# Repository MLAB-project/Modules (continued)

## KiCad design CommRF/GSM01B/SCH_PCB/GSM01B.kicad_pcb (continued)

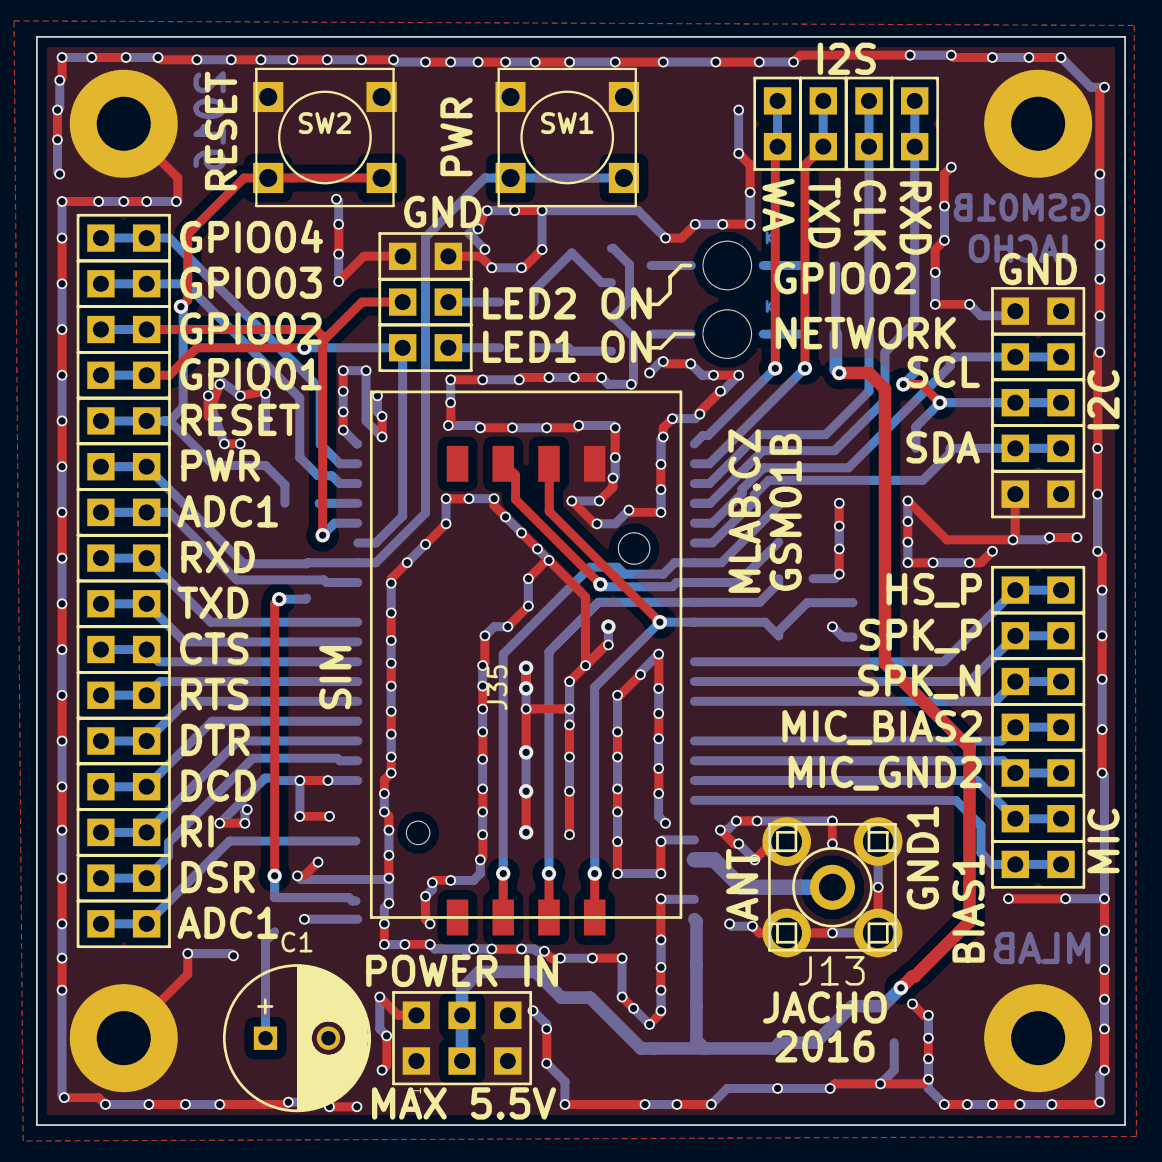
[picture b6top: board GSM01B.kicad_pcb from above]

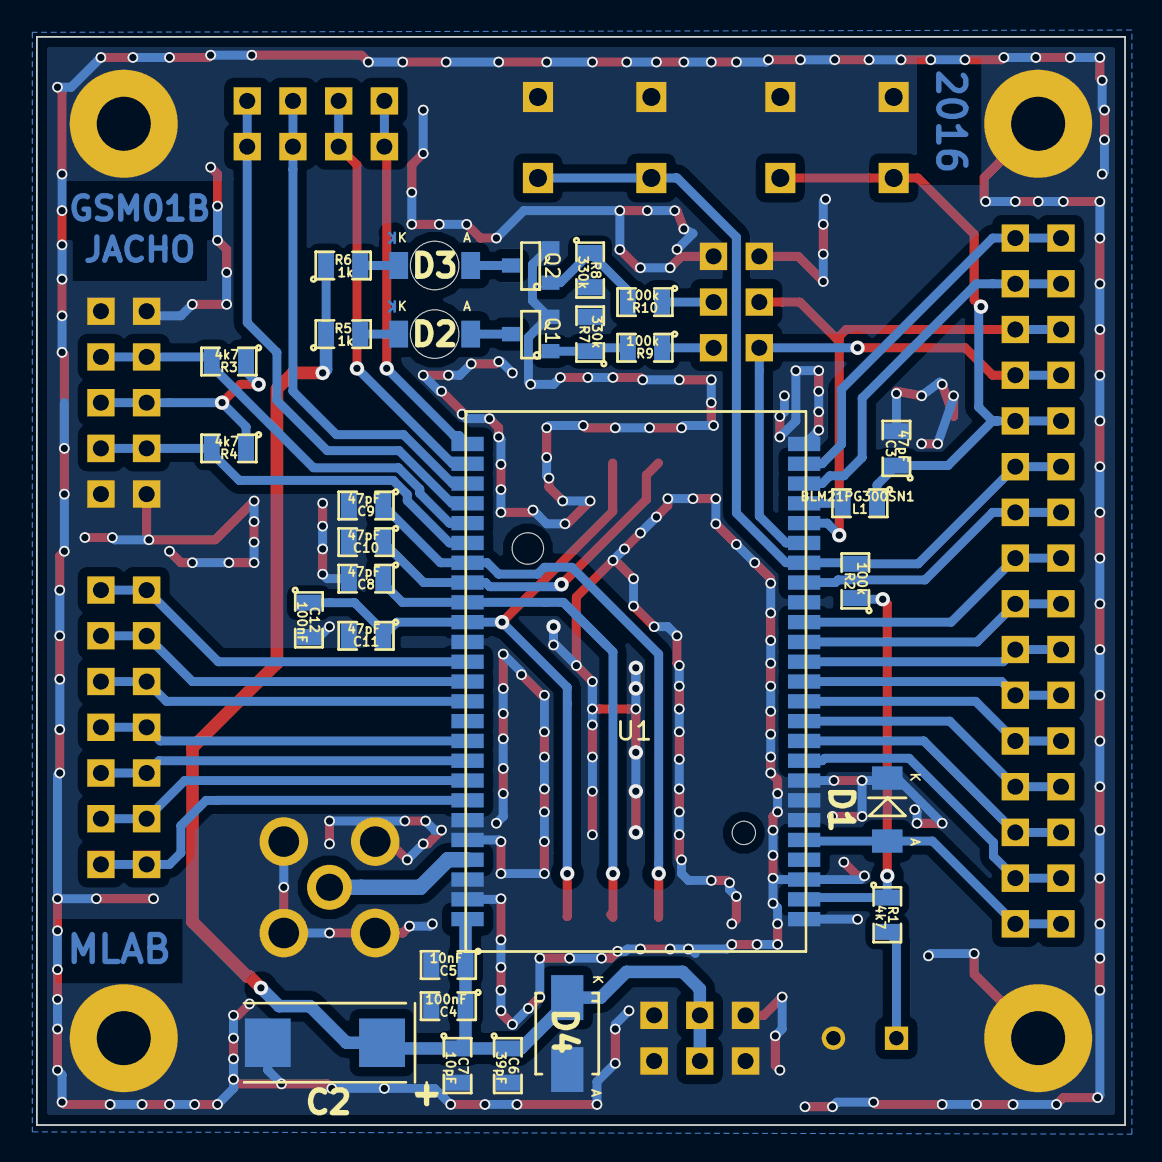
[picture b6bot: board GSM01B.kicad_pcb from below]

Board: 2 copper layers, 60.5 x 60.5 mm, 74 parts (29 on the bottom side), 48 nets.

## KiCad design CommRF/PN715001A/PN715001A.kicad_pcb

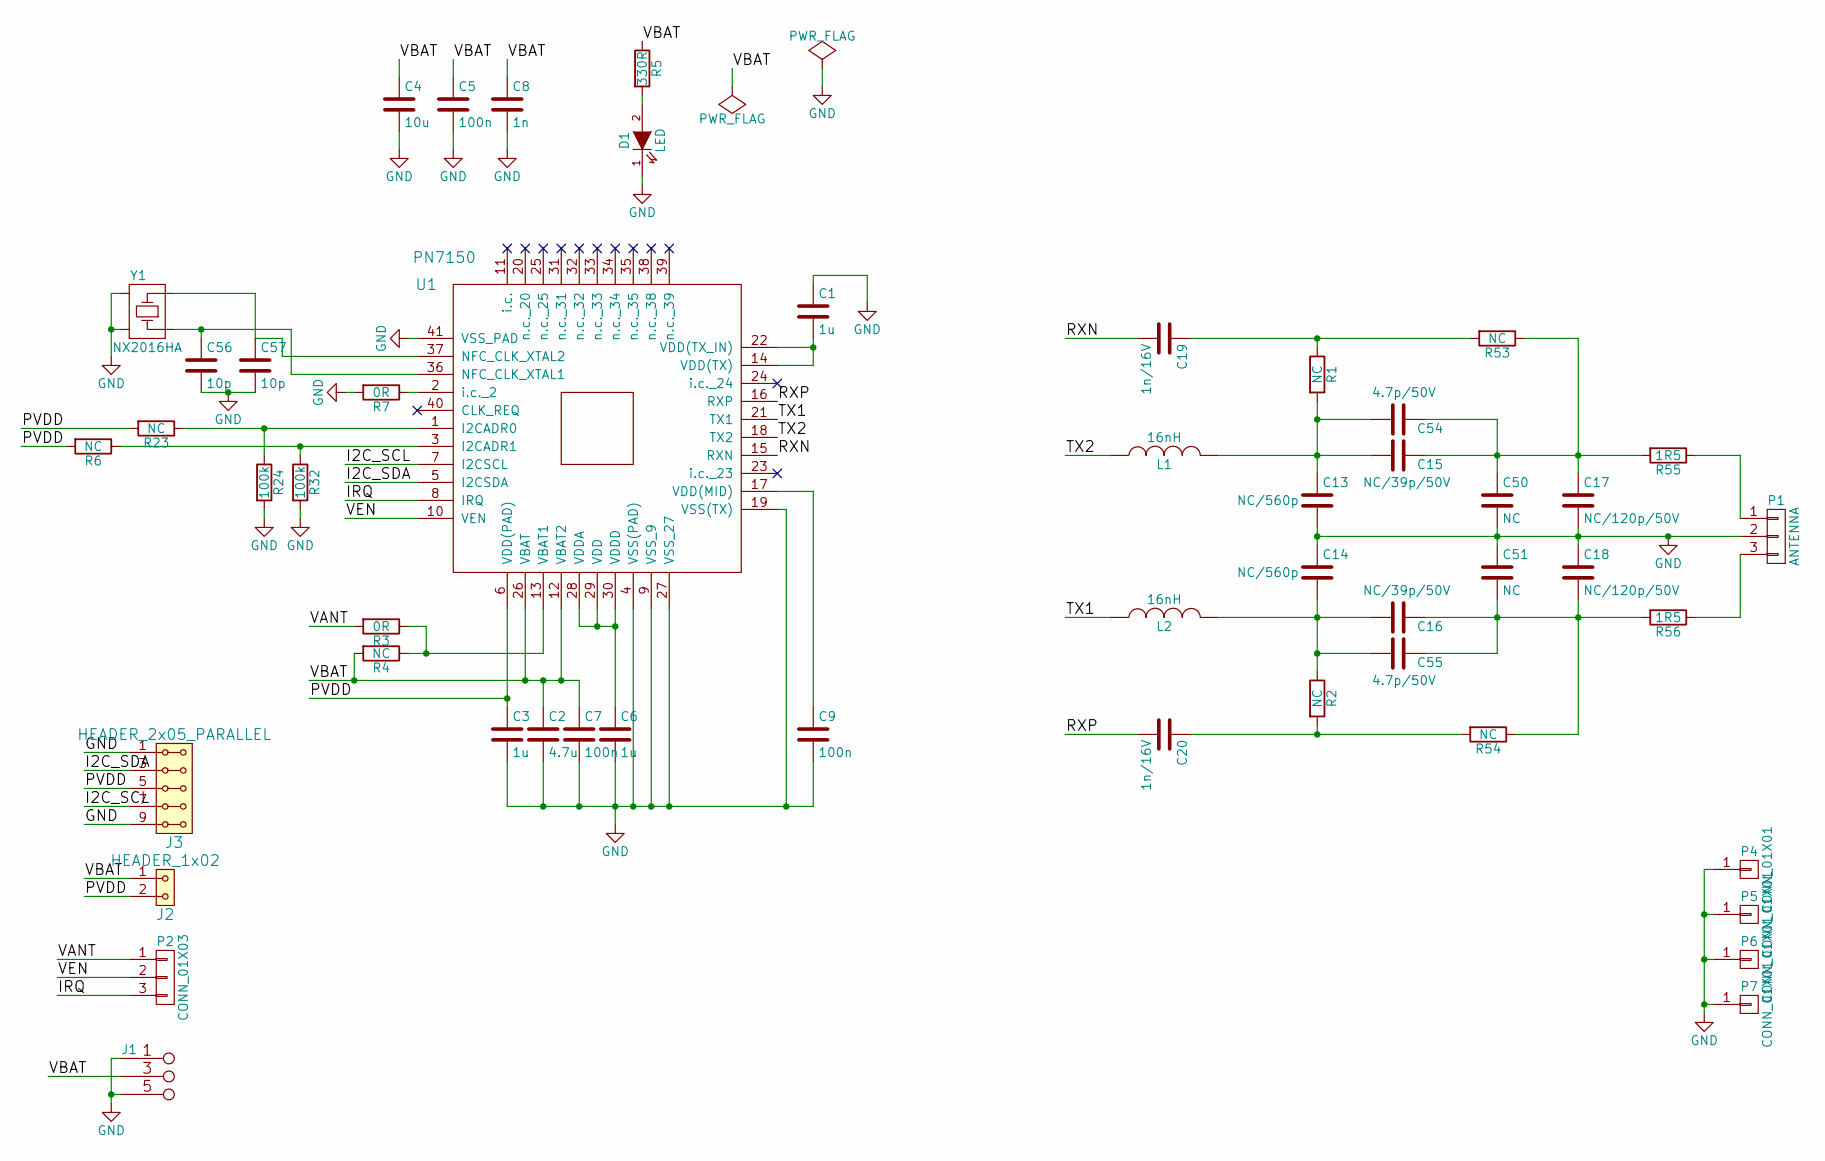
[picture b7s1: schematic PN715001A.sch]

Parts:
C1, C3, C6: 1u; C_0603
C2: 4.7u; C_0603
C4: 10u; C_0805
C5, C7, C9: 100n; C_0603
C8: 1n; C_0603
C13, C14: NC/560p; C_0603
C15, C16: NC/39p/50V; C_0603
C17, C18: NC/120p/50V; C_0603
C19, C20: 1n/16V; C_0603
C50, C51: NC; C_0603
C54, C55: 4.7p/50V; C_0603
C56, C57: 10p; C_0603
D1: LED; LED_1206
J1: PWR +3.3V; Straight_2x03
J2: HEADER_1x02; Straight_1x02
J3: HEADER_2x05_PARALLEL; Straight_2x05
L1, L2: 16nH; R_0603
P1: ANTENNA; Straight_1x03
P2: CONN_01X03; Straight_1x03
P4, P5, P6, P7: CONN_01X01; MountingHole_3mm
R1, R2, R4, R6, R23, R53, R54: NC; R_0603
R3, R7: 0R; R_0603
R5: 330R; R_0603
R24, R32: 100k; R_0603
R55, R56: 1R5; R_0603
U1: PN7150; QFN-40-1EP_6x6mm_Pitch0.5mm
Y1: NX2016HA

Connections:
/I2C_SCL: J3.7, J3.8, U1.7 (I2CSCL)
/I2C_SDA: J3.3, J3.4, U1.5 (I2CSDA)
/IRQ: P2.3, U1.8 (IRQ); also elsewhere on the board
/PVDD: C3.1, J2.2, J3.5, J3.6, R6.2, R23.2, U1.6 (VDD(PAD))
/RXN: C19.2, U1.15 (RXN)
/RXP: C20.2, U1.16 (RXP)
/TX1: L2.1, U1.21 (TX1)
/TX2: L1.1, U1.18 (TX2)
/VANT: C1.2, U1.14 (VDD(TX)), U1.22 (VDD(TX_IN)); also elsewhere on the board
/VBAT: C2.1, C4.1, C5.1, C7.1, C8.1, J1.3 (4), J1.4, J2.1, R4.2, R5.1, U1.12 (VBAT2), U1.26 (VBAT)
/VEN: P2.2, U1.10 (VEN); also elsewhere on the board
GND: C1.1, C2.2, C3.2, C4.2, C5.2, C6.2, C7.2, C8.2, C9.2, C13.2, C14.1, C17.2, C18.1, C50.2, C51.1, C56.2, C57.2, D1.1 (K), J1.1 (2), J1.2, J1.5 (6), J1.6, J3.1, J3.2, J3.9, J3.10, P1.2, P4.1, P5.1, P6.1, P7.1, R7.2, R24.2, R32.2, U1.4 (VSS(PAD)), U1.9 (VSS_9), U1.19 (VSS(TX)), U1.27 (VSS_27), U1.41 (VSS_PAD), Y1.2, Y1.4
unnamed: C6.1, U1.28 (VDDA), U1.29 (VDD), U1.30 (VDDD)
unnamed: C9.1, U1.17 (VDD(MID))
unnamed: C13.1, C15.2, C54.2, L1.2, R1.2
unnamed: C14.2, C16.2, C55.2, L2.2, R2.1
unnamed: C15.1, C17.1, C50.1, C54.1, R53.1, R55.2
unnamed: C16.1, C18.2, C51.2, C55.1, R54.1, R56.2
unnamed: C19.1, R1.1, R53.2
unnamed: C20.1, R2.2, R54.2
unnamed: C56.1, U1.36 (NFC_CLK_XTAL1), Y1.1
unnamed: C57.1, U1.37 (NFC_CLK_XTAL2), Y1.3
unnamed: D1.2 (A), R5.2
unnamed: P1.1, R55.1
unnamed: P1.3, R56.1
unnamed: P2.1, R3.2
unnamed: R3.1, R4.1, U1.13 (VBAT1)
unnamed: R7.1, U1.2 (i.c._2)
unnamed: R23.1, R24.1, U1.1 (I2CADR0)
unnamed: R6.1, R32.1, U1.3 (I2CADR1)

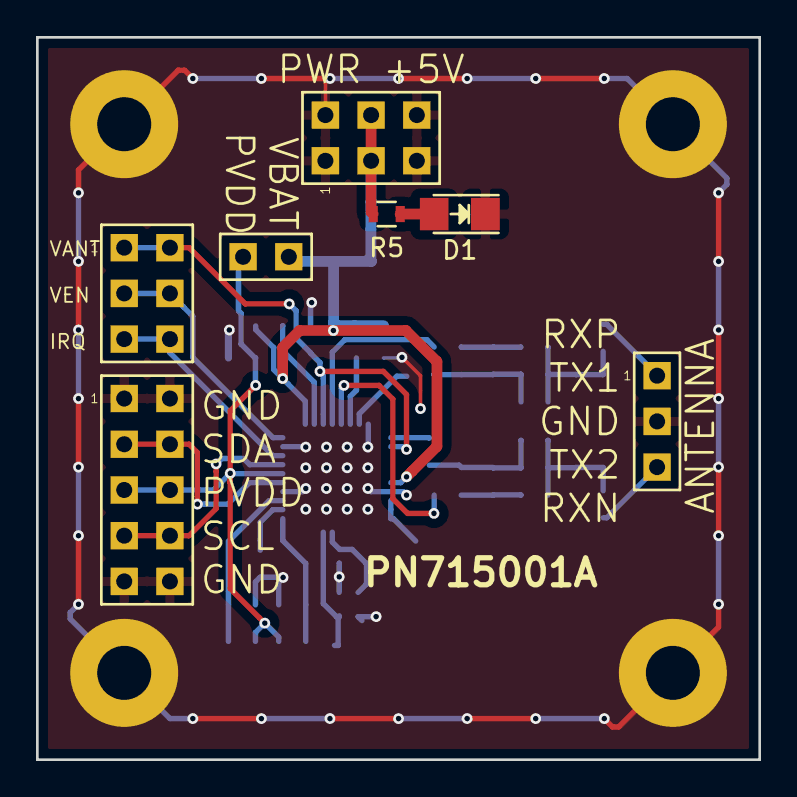
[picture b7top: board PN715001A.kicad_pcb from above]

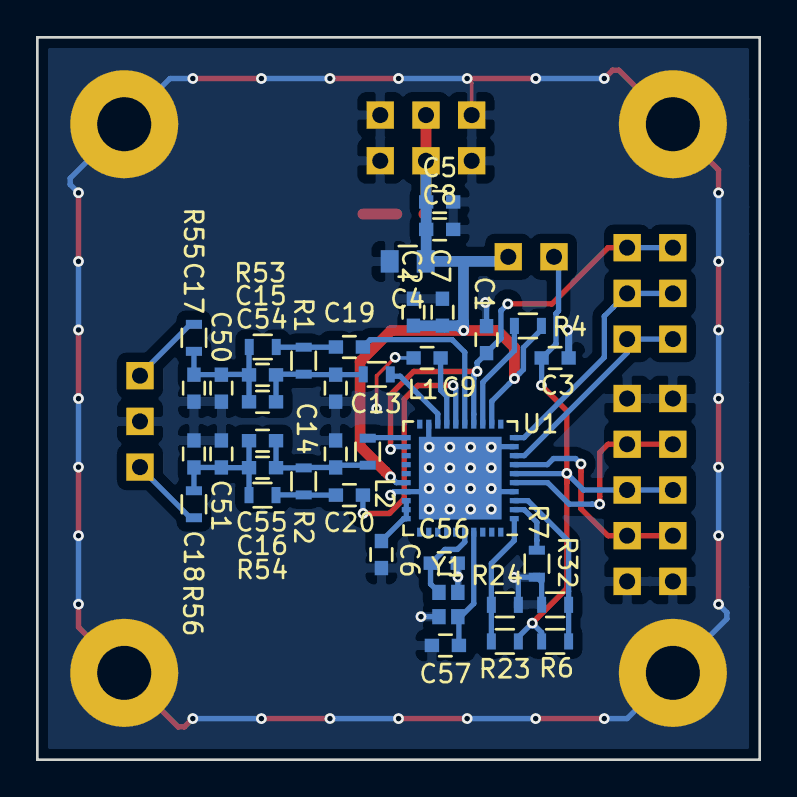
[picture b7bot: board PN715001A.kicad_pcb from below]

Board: 2 copper layers, 40.1 x 40.1 mm, 50 parts (39 on the bottom side), 29 nets.

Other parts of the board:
J4: HEADER_2x03_PARALLEL; Straight_2x03

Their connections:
/IRQ: J4.5, J4.6; also elsewhere on the board
/VANT: J4.1, J4.2; also elsewhere on the board
/VEN: J4.3, J4.4; also elsewhere on the board

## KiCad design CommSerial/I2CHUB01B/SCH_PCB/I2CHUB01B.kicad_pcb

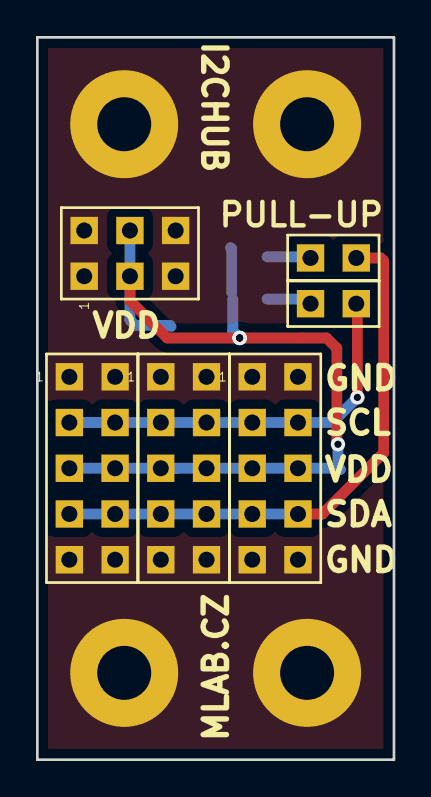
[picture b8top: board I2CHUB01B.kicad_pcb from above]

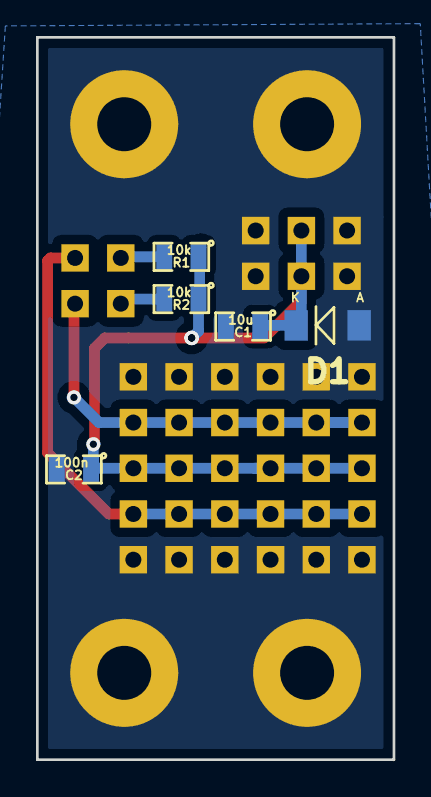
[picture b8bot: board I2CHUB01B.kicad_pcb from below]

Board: 2 copper layers, 19.8 x 40.1 mm, 15 parts (5 on the bottom side), 6 nets.

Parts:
C1: 10u; SMD-0805
C2: 100n; SMD-0805
D1: BZV55C; Diode-MiniMELF_Standard
J1: JUMP_3X2; Straight_2x03
J2, J3, J4: JUMP_5X2; Straight_2x05
J5, J6: CONN_2; Straight_1x02
M1, M2, M3, M4: HOLE; MountingHole_3mm
R1, R2: 10k; SMD-0805

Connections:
/SCL: J2.3, J2.4, J3.3, J3.4, J4.3, J4.4, J6.2
/SDA: J2.7, J2.8, J3.7, J3.8, J4.7, J4.8, J5.2
GND: C1.2, C2.2, D1.1, J1.1, J1.2, J1.5, J1.6, J2.1, J2.2, J2.9, J2.10, J3.1, J3.2, J3.9, J3.10, J4.1, J4.2, J4.9, J4.10, M1.1, M2.1, M3.1, M4.1
unnamed: J5.1, R1.2
unnamed: J6.1, R2.2
VCC: C1.1, C2.1, D1.2, J1.3, J1.4, J2.5, J2.6, J3.5, J3.6, J4.5, J4.6, R1.1, R2.1
